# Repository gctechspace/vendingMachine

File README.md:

# vendingMachine

**************************Version 2******12/17***************
It's Been awhile ;-)
PCB needs a massive update!!! but will still work *enough*.
Moving to a Nextion 2.4" Touch Screen display and ditching the old Keypad.
Will probably move to an ESP32/8266 for Comms.
......More To Come

**************************Version 1******12/14***************
A Vending machine system using:
Atmega1284
Coin Selector <= Accepts 50c, $1 & $2
2.4" QVga tft <= Price & Info Display
SDCard	      <= Stock List & info
RFID Reader   <= For member discount & management functions
Breakouts for:
Bluetooth
NRF24L01 Radio's
ESP01 Wifi module
Intergrates with old keypad

Use's Shift registers to control despencing of Items.
Motors are multiplexed with Highside drivers and transistor arrays.
All Motor circuit have been changed to allow despence detection and allow
tray removal detection.

Project By...
SkipXtian
MickMorri
JamesSapsford
Spidie

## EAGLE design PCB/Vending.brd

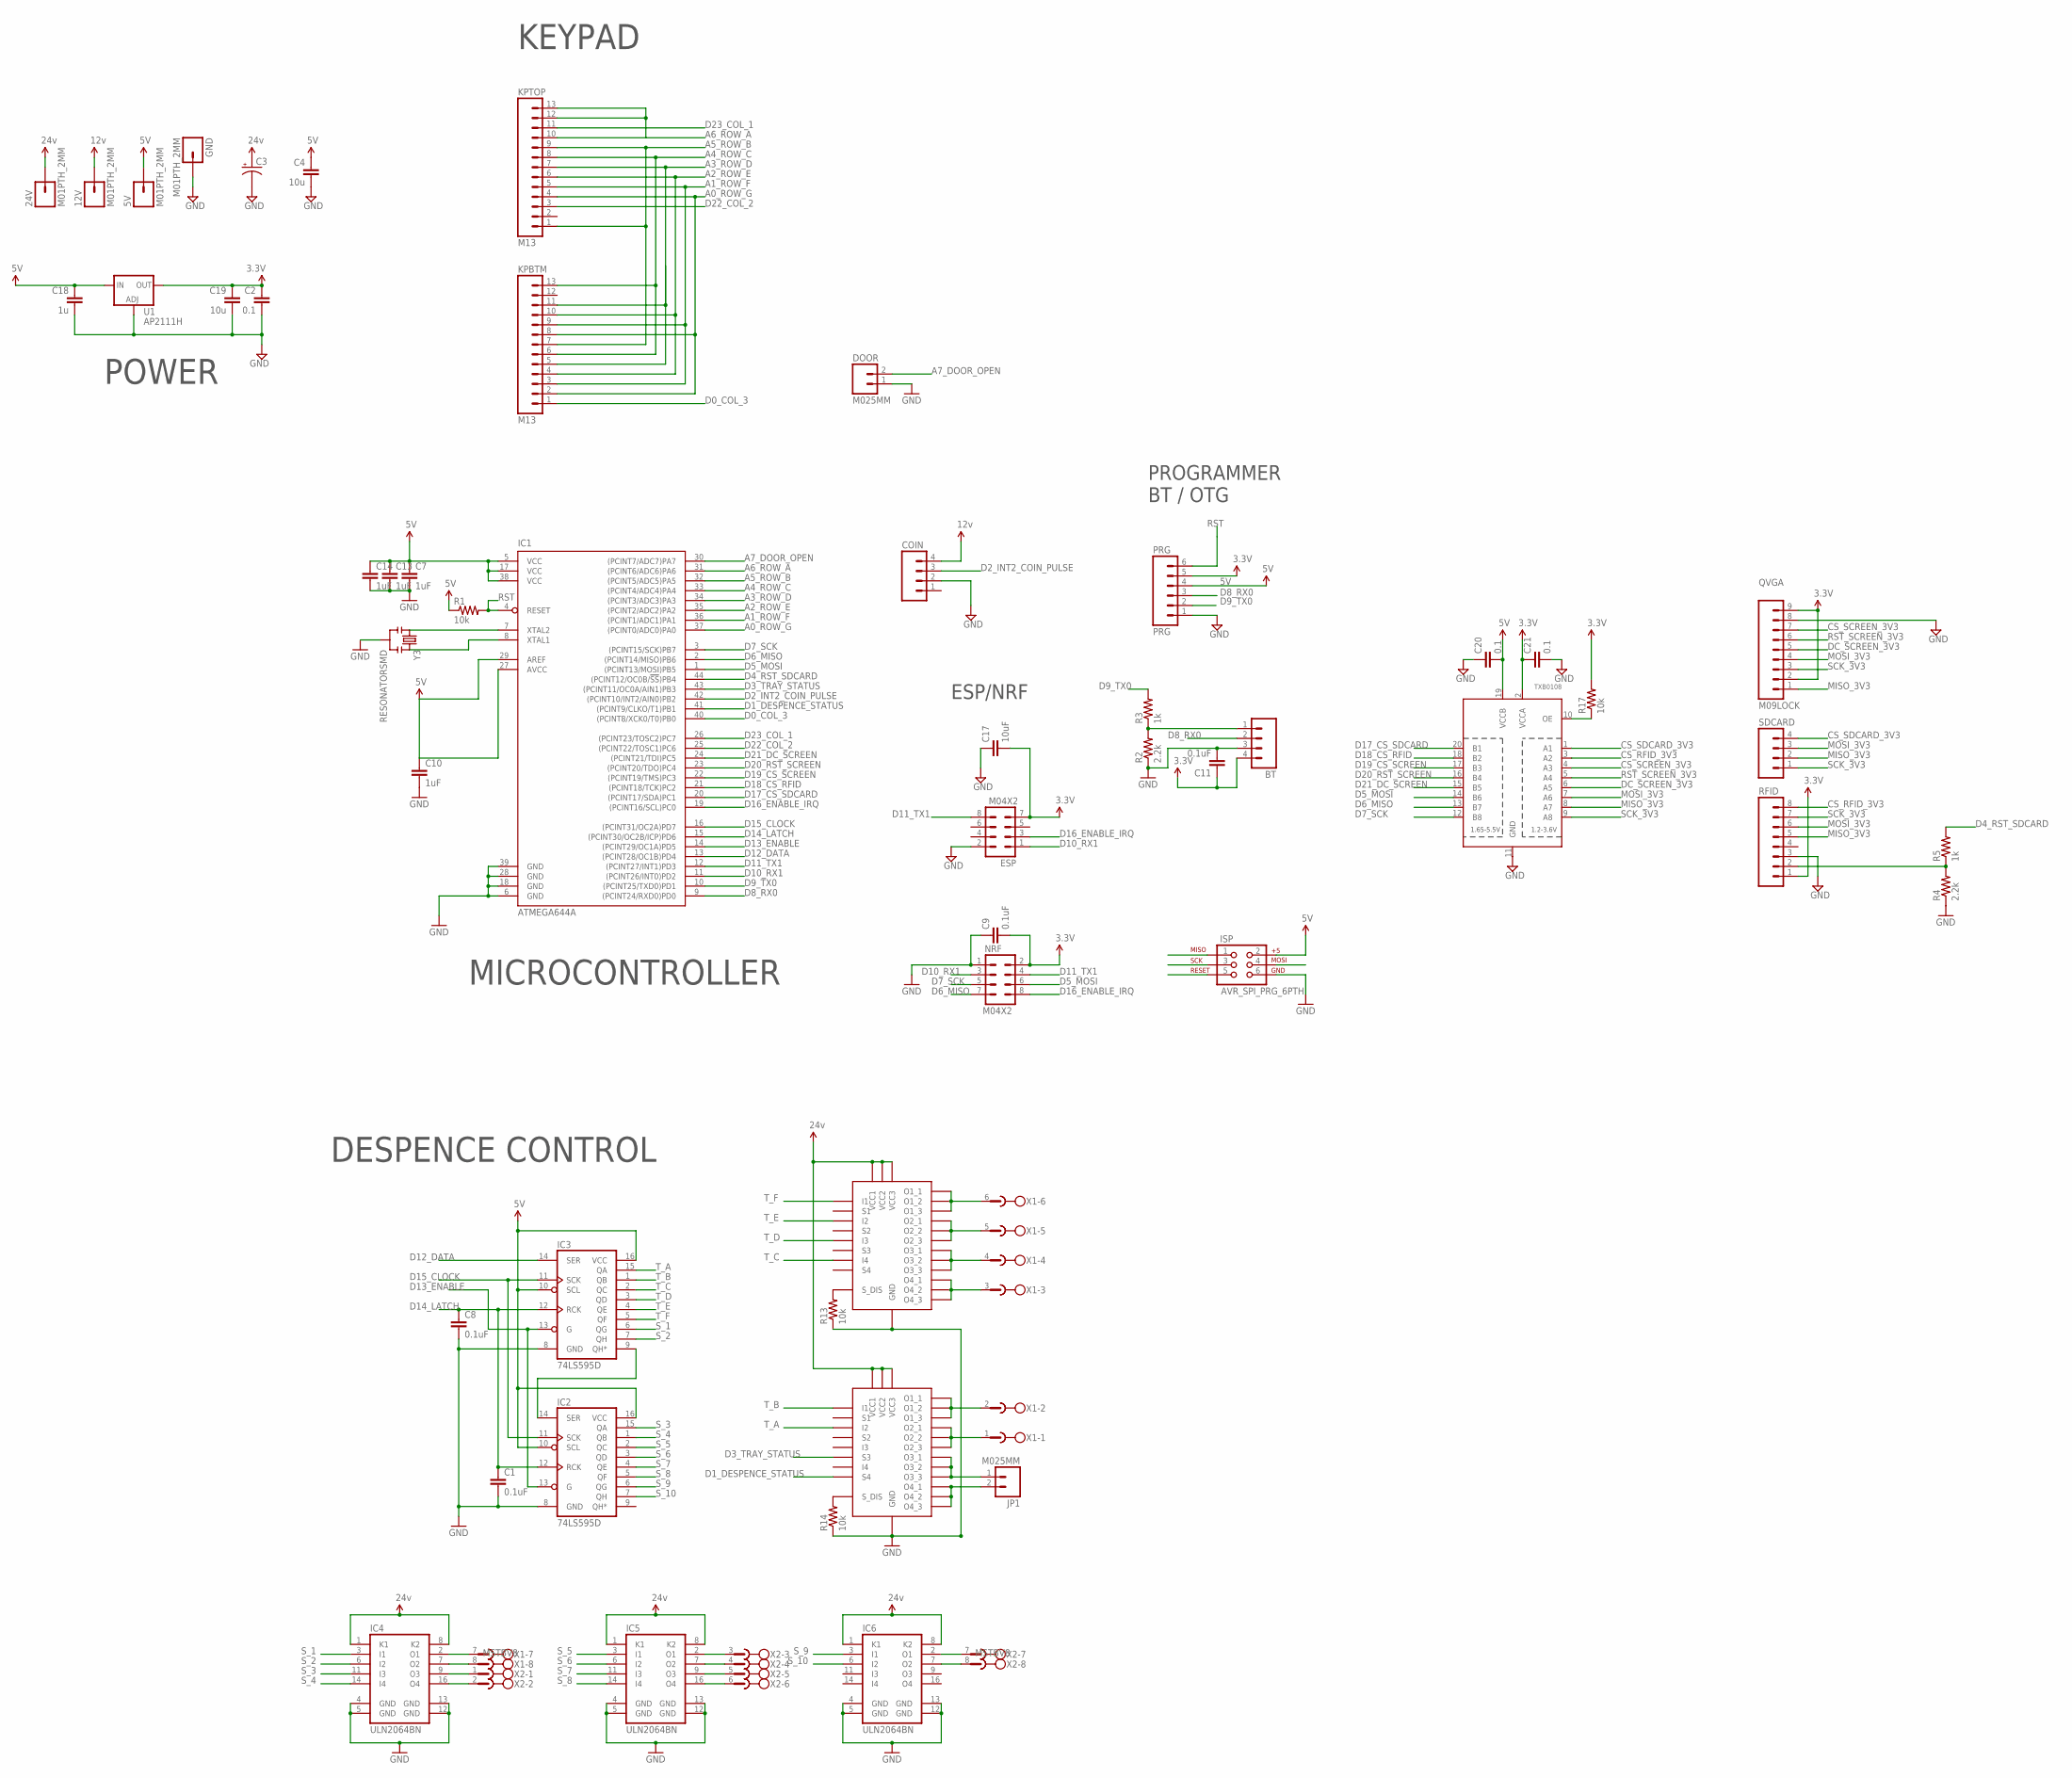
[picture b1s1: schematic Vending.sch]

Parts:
5V, 12V, 24V: M01PTH_2MM; 1X01_2MM
BT: M04PTH; 1X04
C1, C8, C9, C11: 0.1uF; 0805
C2, C20, C21: 0.1; 0805
C3: CAP_POLPTH4; CPOL-RADIAL-1000UF-25V
C4, C19: 10u; 0805-CAP
C7, C10, C13, C14: 1uF; 0805
C17: 10uF; 0805
C18: 1u; 0805
COIN: M04PTH; 1X04
DOOR: M025MM; SCREWTERMINAL-5MM-2
ESP: M04X2; 2X4
GND: M01PTH_2MM; 1X01_2MM
IC1: ATMEGA644A; TQFP44
IC2, IC3: 74LS595D; SO16
IC4, IC5, IC6: ULN2064BN; DIL16
ISP: AVR_SPI_PRG_6PTH; 2X3
JP1: M025MM; SCREWTERMINAL-5MM-2
KPBTM: M13; 1X13
KPTOP: M13; 1X13
NRF: M04X2; 2X4
PRG: PRG; 1X06
QVGA: M09LOCK; 1X09_LOCK
R1, R13, R14, R17: 10k; 0805
R2, R4: 2.2k; 0805
R3, R5: 1k; 0805
RFID: M08LOCK; 1X08_LOCK
SDCARD: M04LOCK; 1X04_LOCK
TXB0108: TXB0108PWR; TSSOP20
U1: AP2111H; SOT223
U$2, U$3: VNQ5E160K-E; POWERS0-24
X1: MSTBV8
X2: MSTBV8; MPN MSTBV 2,5/8-GF-5.08
Y3: RESONATORSMD; RESONATOR-SMD

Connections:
3.3V: BT.4, C2.1, C9.2, C11.1, C17.2, C19.1, C21.1, ESP.7, NRF.2, PRG.5, QVGA.2, QVGA.9, R17.2, RFID.1, TXB0108.2 (VCCA), U1.2 (OUT)
5V: 5V.1, C4.1, C7.1, C10.1, C13.1, C14.1, C18.1, C20.2, IC1.5 (VCC), IC1.17 (VCC), IC1.27 (AVCC), IC1.29 (AREF), IC1.38 (VCC), IC2.10 (SCL), IC2.16 (VCC), IC3.10 (SCL), IC3.16 (VCC), ISP.2, PRG.4, R1.1, TXB0108.19 (VCCB), U1.3 (IN)
12V: 12V.1, COIN.4
24V: 24V.1, C3.1 (+), IC4.1 (K1), IC4.8 (K2), IC5.1 (K1), IC5.8 (K2), IC6.1 (K1), IC6.8 (K2), U$2.1 (VCC1), U$2.12 (VCC2), U$2.VCC (VCC3), U$3.1 (VCC1), U$3.12 (VCC2), U$3.VCC (VCC3)
A0_ROW_G: IC1.37 ((PCINT0/ADC0)PA0), KPBTM.2, KPBTM.8, KPTOP.4
A1_ROW_F: IC1.36 ((PCINT1/ADC1)PA1), KPBTM.3, KPBTM.9, KPTOP.5
A2_ROW_E: IC1.35 ((PCINT2/ADC2)PA2), KPBTM.4, KPBTM.10, KPTOP.6
A3_ROW_D: IC1.34 ((PCINT3/ADC3)PA3), KPBTM.5, KPBTM.11, KPTOP.7
A4_ROW_C: IC1.33 ((PCINT4/ADC4)PA4), KPBTM.6, KPBTM.13, KPTOP.8
A5_ROW_B: IC1.32 ((PCINT5/ADC5)PA5), KPBTM.7, KPTOP.1, KPTOP.9
A6_ROW_A: IC1.31 ((PCINT6/ADC6)PA6), KPTOP.10, KPTOP.12, KPTOP.13
A7_DOOR_OPEN: DOOR.2, IC1.30 ((PCINT7/ADC7)PA7)
CS_RFID_3V3: RFID.8, TXB0108.3 (A2)
CS_SCREEN_3V3: QVGA.7, TXB0108.4 (A3)
CS_SDCARD_3V3: SDCARD.4, TXB0108.1 (A1)
D0_COL_3: IC1.40 ((PCINT8/XCK0/T0)PB0), KPBTM.1
D1_DESPENCE_STATUS: IC1.41 ((PCINT9/CLKO/T1)PB1), U$3.10 (S4)
D2_INT2_COIN_PULSE: COIN.3, IC1.42 ((PCINT10/INT2/AIN0)PB2)
D3_TRAY_STATUS: IC1.43 ((PCINT11/OC0A/AIN1)PB3), U$3.8 (S3)
D4_RST_SDCARD: IC1.44 ((PCINT12/OC0B/!SS!)PB4), R5.2
D5_MOSI: IC1.1 ((PCINT13/MOSI)PB5), ISP.4, NRF.6, TXB0108.14 (B6)
D6_MISO: IC1.2 ((PCINT14/MISO)PB6), ISP.1, NRF.7, TXB0108.13 (B7)
D7_SCK: IC1.3 ((PCINT15/SCK)PB7), ISP.3, NRF.5, TXB0108.12 (B8)
D8_RX0: BT.2, IC1.9 ((PCINT24/RXD0)PD0), PRG.3
D9_TX0: IC1.10 ((PCINT25/TXD0)PD1), PRG.2, R3.2
D10_RX1: ESP.1, IC1.11 ((PCINT26/INT0)PD2), NRF.3
D11_TX1: ESP.8, IC1.12 ((PCINT27/INT1)PD3), NRF.4
D12_DATA: IC1.13 ((PCINT28/OC1B)PD4), IC3.14 (SER)
D13_ENABLE: IC1.14 ((PCINT29/OC1A)PD5), IC2.13 (G), IC3.13 (G)
D14_LATCH: C1.1, C8.1, IC1.15 ((PCINT30/OC2B/ICP)PD6), IC2.12 (RCK), IC3.12 (RCK)
D15_CLOCK: IC1.16 ((PCINT31/OC2A)PD7), IC2.11 (SCK), IC3.11 (SCK)
D16_ENABLE_IRQ: ESP.3, IC1.19 ((PCINT16/SCL)PC0), NRF.8
D17_CS_SDCARD: IC1.20 ((PCINT17/SDA)PC1), TXB0108.20 (B1)
D18_CS_RFID: IC1.21 ((PCINT18/TCK)PC2), TXB0108.18 (B2)
D19_CS_SCREEN: IC1.22 ((PCINT19/TMS)PC3), TXB0108.17 (B3)
D20_RST_SCREEN: IC1.23 ((PCINT20/TDO)PC4), TXB0108.16 (B4)
D21_DC_SCREEN: IC1.24 ((PCINT21/TDI)PC5), TXB0108.15 (B5)
D22_COL_2: IC1.25 ((PCINT22/TOSC1)PC6), KPTOP.3
D23_COL_1: IC1.26 ((PCINT23/TOSC2)PC7), KPTOP.11
DC_SCREEN_3V3: QVGA.5, TXB0108.6 (A5)
GND: BT.3, C1.2, C2.2, C3.2 (-), C4.2, C7.2, C8.2, C9.1, C10.2, C11.2, C13.2, C14.2, C17.1, C18.2, C19.2, C20.1, C21.2, COIN.2, DOOR.1, ESP.2, GND.1, IC1.6 (GND), IC1.18 (GND), IC1.28 (GND), IC1.39 (GND), IC2.8 (GND), IC3.8 (GND), IC4.4 (GND), IC4.5 (GND), IC4.12 (GND), IC4.13 (GND), IC5.4 (GND), IC5.5 (GND), IC5.12 (GND), IC5.13 (GND), IC6.4 (GND), IC6.5 (GND), IC6.12 (GND), IC6.13 (GND), ISP.6, NRF.1, PRG.1, QVGA.8, R2.1, R4.1, R13.1, R14.1, RFID.3, TXB0108.11 (GND), U1.1 (ADJ), U$2.2 (GND), U$3.2 (GND), Y3.2
MISO_3V3: QVGA.1, RFID.5, SDCARD.2, TXB0108.8 (A7)
MOSI_3V3: QVGA.4, RFID.6, SDCARD.3, TXB0108.7 (A6)
unnamed: IC2.14 (SER), IC3.9 (QH*)
unnamed: IC1.7 (XTAL2), Y3.1
unnamed: IC1.8 (XTAL1), Y3.3
unnamed: IC4.9 (O3), X2.1
unnamed: IC4.2 (O1), X1.7
unnamed: BT.1, R2.2, R3.1
unnamed: IC4.7 (O2), X1.8
unnamed: IC4.16 (O4), X2.2
unnamed: IC5.2 (O1), X2.3
unnamed: IC5.7 (O2), X2.4
unnamed: IC6.2 (O1), X2.7
unnamed: IC6.7 (O2), X2.8
unnamed: R13.2, U$2.11 (S_DIS)
unnamed: R14.2, U$3.11 (S_DIS)
unnamed: R4.2, R5.1, RFID.2
unnamed: U$3.22 (O1_3), U$3.23 (O1_2), U$3.24 (O1_1), X1.2
unnamed: U$3.19 (O2_3), U$3.20 (O2_2), U$3.21 (O2_1), X1.1
unnamed: IC5.9 (O3), X2.5
unnamed: IC5.16 (O4), X2.6
unnamed: R17.1, TXB0108.10 (OE)
P1: U$2.22 (O1_3), U$2.23 (O1_2), U$2.24 (O1_1), X1.6
P2: U$2.19 (O2_3), U$2.20 (O2_2), U$2.21 (O2_1), X1.5
P3: U$2.16 (O3_3), U$2.17 (O3_2), U$2.18 (O3_1), X1.4
P4: U$2.13 (O4_3), U$2.14 (O4_2), U$2.15 (O4_1), X1.3
P7: JP1.1, U$3.16 (O3_3), U$3.17 (O3_2), U$3.18 (O3_1)
P8: JP1.2, U$3.13 (O4_3), U$3.14 (O4_2), U$3.15 (O4_1)
RST: IC1.4 (RESET), ISP.5, PRG.6, R1.2
RST_SCREEN_3V3: QVGA.6, TXB0108.5 (A4)
SCK_3V3: QVGA.3, RFID.7, SDCARD.1, TXB0108.9 (A8)
S_1: IC3.6 (QG), IC4.3 (I1)
S_2: IC3.7 (QH), IC4.6 (I2)
S_3: IC2.15 (QA), IC4.11 (I3)
S_4: IC2.1 (QB), IC4.14 (I4)
S_5: IC2.2 (QC), IC5.3 (I1)
S_6: IC2.3 (QD), IC5.6 (I2)
S_7: IC2.4 (QE), IC5.11 (I3)
S_8: IC2.5 (QF), IC5.14 (I4)
S_9: IC2.6 (QG), IC6.3 (I1)
S_10: IC2.7 (QH), IC6.6 (I2)
T_A: IC3.15 (QA), U$3.5 (I2)
T_B: IC3.1 (QB), U$3.3 (I1)
T_C: IC3.2 (QC), U$2.9 (I4)
T_D: IC3.3 (QD), U$2.7 (I3)
T_E: IC3.4 (QE), U$2.5 (I2)
T_F: IC3.5 (QF), U$2.3 (I1)

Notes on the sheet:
DESPENCE CONTROL
KEYPAD
MICROCONTROLLER
POWER
ESP/NRF
PROGRAMMER BT / OTG

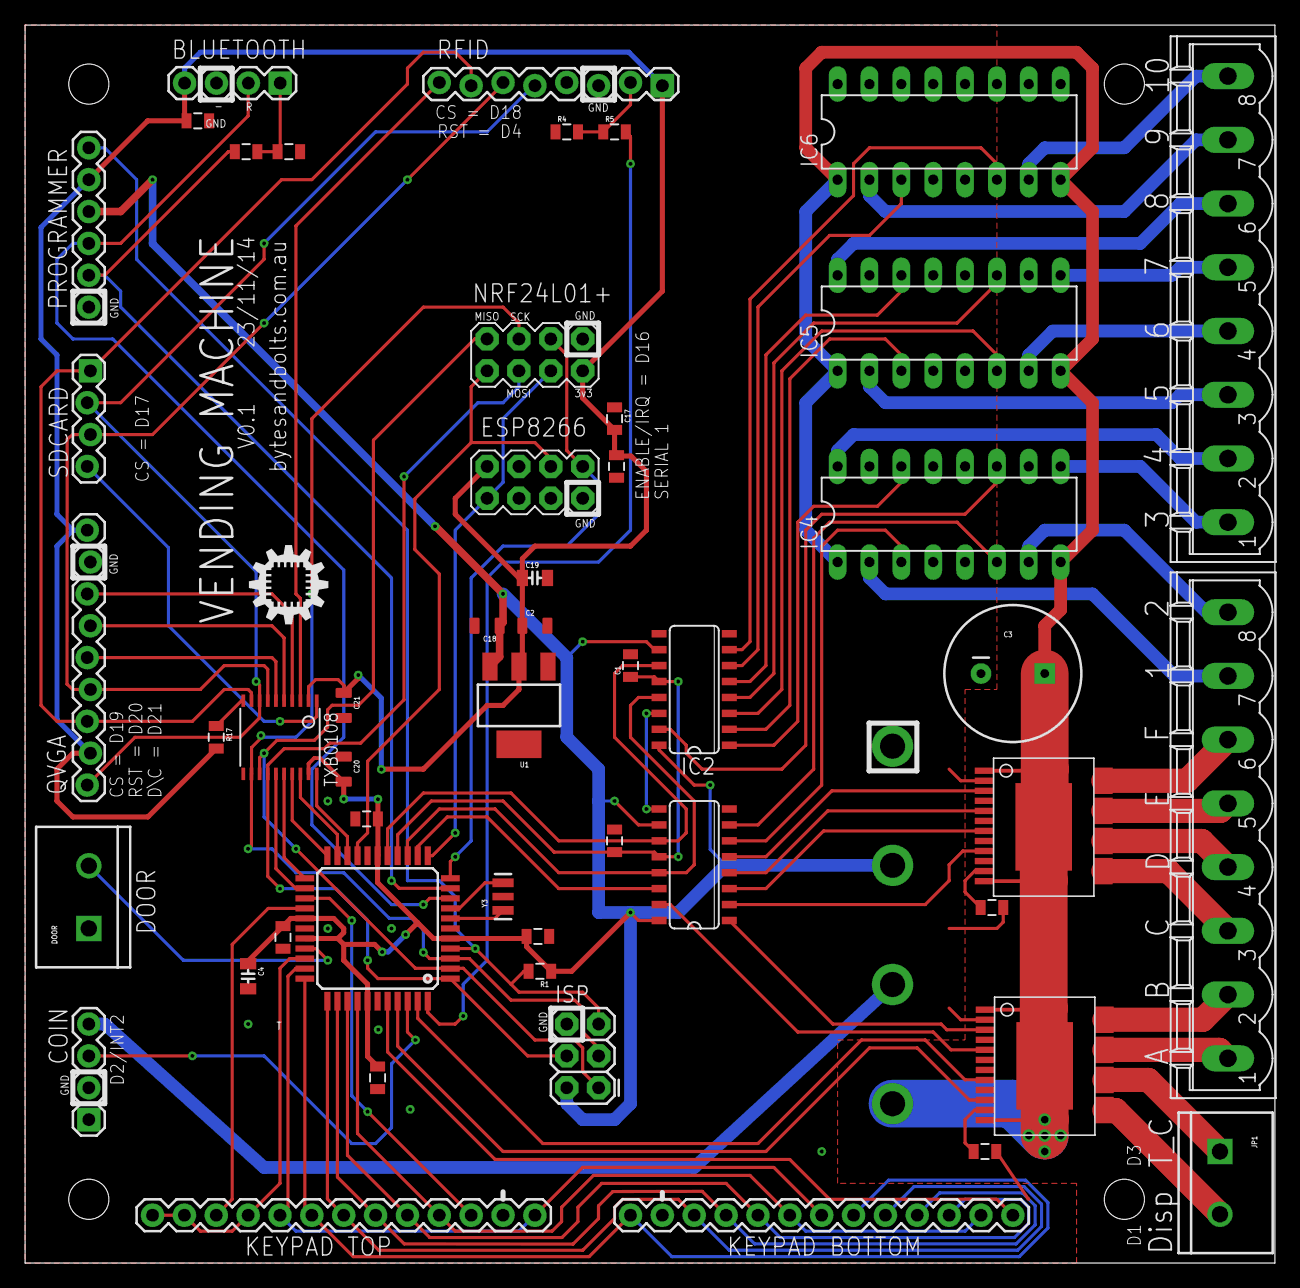
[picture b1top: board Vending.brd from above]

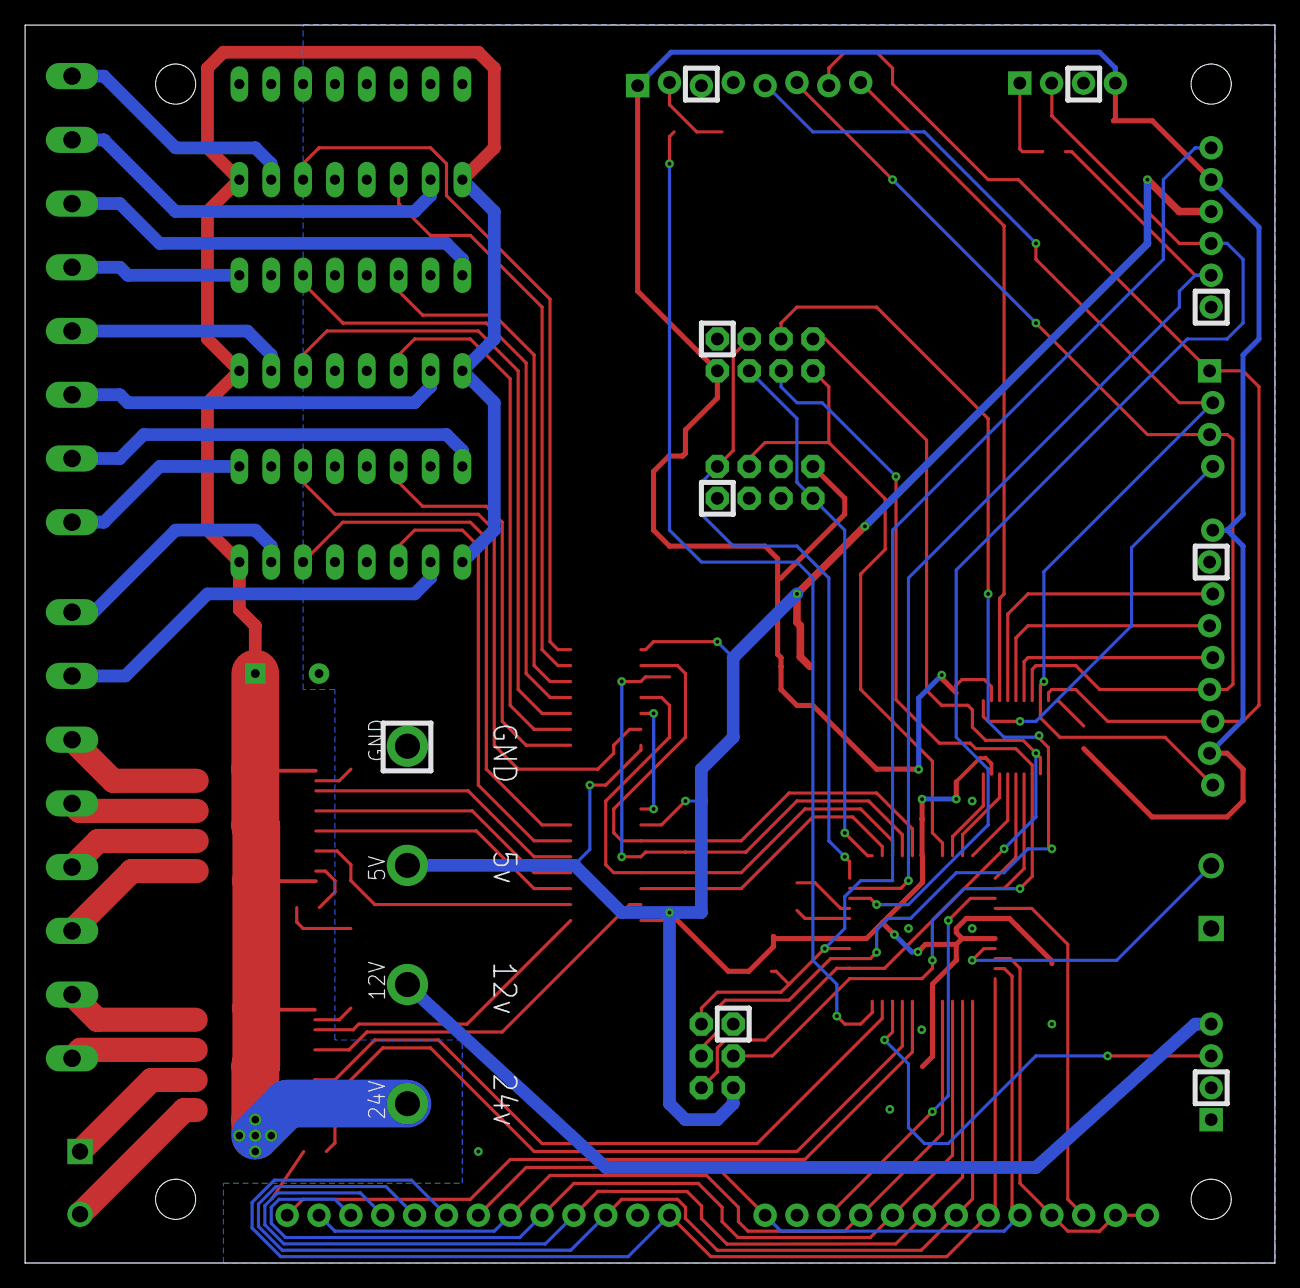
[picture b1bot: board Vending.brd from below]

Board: 2 copper layers, 99.6 x 98.7 mm, 55 parts (4 on the bottom side), 88 nets.

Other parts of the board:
U$1: ID_LOGO_X0.25

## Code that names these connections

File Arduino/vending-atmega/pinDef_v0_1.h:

//Pin defines for Board Version 0.1  -  23/11/14

//PB0-7
#define KP_Col3        0
#define despenceStatus 1 //24v so INVERTED
#define coinIn         2
#define trayStatus     3 //24v so INVERTED
#define RFID_RST       4 //MUST BE OUTPUT
#define HW_MOSI        5
#define HW_MISO        6
#define HW_SCK         7

//PD0-7
#define HW_Rx          8
#define HW_Tx          9
#define ESP_Rx         10
#define ESP_Tx         11
#define Shift_DATA     12
#define Shift_ENABLE   13
#define Shift_LATCH    14
#define Shift_CLOCK    15

//PC0-7
#define ESP_ENABLE     16
#define SDCard_CS      17
#define RFID_CS        18
#define QVGA_CS        19
#define QVGA_RST       20
#define QVGA_DC        21
#define KP_Col2        22
#define KP_Col1        23

//PA0-7
#define KP_RowG        24//A0
#define KP_RowF        25//A1
#define KP_RowE        26//A2
#define KP_RowD        27//A3
#define KP_RowC        28//A4
#define KP_RowB        29//A5
#define KP_RowA        30//A6
#define doorStatus     31//A7

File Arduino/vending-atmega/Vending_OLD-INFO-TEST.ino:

/* OLD CODE FOR TESTING MOTORS ETC - REFERENCE ONLY
const int enablePin = 13;
const int latchPin = 14;
const int clockPin = 15;
const int dataPin = 12;
const int IO1_Output = 11;
const int IO1_Status = 10;
const int IO2_Output = 26;
const int IO2_Status = 27;   //STATUS will go LOW when it has INPUT
const int IO3_Status = 1;
const int IO4_Status = 0;
const int IO5_Status = 23;
const int IO6_Status = 22;
const int IO7_Status = 21;
const int IO8_Status = 20;
const int IO9_Status = 19;
const int IO10_Status = 18;
const int watchDog = 16;

const int Selector = A0;  // Analog input pin that the voltage divider is attached to
const int selPwr = A1;    //Control of the NPN for the voltage dividers power

#define despenceTime 10000

void setup()
{
  //SETUP PORT INPUTS
  DDRC &= ~0xFC; //Set PC7-2 as OUTPUTS, FC=11111100  Doesn't affect the "0's"
  PORTC |= 0xFC; //Enable Pull Ups
  DDRB &= 0x03;  //set PB0-1 as OUTPUTS, 03=00000011
  PORTB |= 0x03;  //Enable Pull Ups
  DDRA &= 0xFC;
  //SETUP SHIFT REG
  //DDRD |= 0xF0;  //set PD4-7 as OUTPUTS, 0F=11110000
  //PORTD &= ~0x20; //set D13 (PD5) LOW
  pinMode(enablePin, OUTPUT);
  digitalWrite(enablePin, HIGH);  //Enabled Low = ON, HIGH = OFF
  pinMode(latchPin, OUTPUT);
  pinMode(dataPin, OUTPUT);
  pinMode(clockPin, OUTPUT);
  pinMode(IO1_Output, OUTPUT);  //D11
  pinMode(IO1_Status, INPUT);   //D10
  digitalWrite(IO1_Status, HIGH);     //Enable pull up
  pinMode(IO2_Output, OUTPUT);  //D26
  pinMode(IO2_Status, INPUT);   //D27
  digitalWrite(IO2_Status, HIGH);     //Enable pull up
  pinMode(watchDog, INPUT);  //SETUP PIN as watchDog


  Serial.begin(9600); //For Debugging & bluetooth
  Serial.println("Vending Test");



    pinMode(3, OUTPUT);

}

void loop()
{

  if(Serial.available() > 0) {
    byte traySelect = (1 << (Serial.read()-65)); //Converts the Row (A-F) into a binary (1-32)
    delay(100);
    byte slotSelect = processSlot(Serial.read());

    if(despence(traySelect, slotSelect)){
      Serial.println("Worked");
    } else {
      Serial.println("Error");
    }
  }
  //Serial.println(traySelect);
  //Serial.println(slotSelect);
}



byte processSlot(char inChar){
  if (inChar >= '1' && inChar <= '9'){
    return inChar-48;
  } else if (inChar == '0'){
    return 10;
  }
}

boolean despence(byte tray, byte slot){
  unsigned long despenceStart = 0;
  powerIO(tray);
  PORTA = (1 << (slot+1));  //the +1 is for testing as A2 is the first pin we are using on that port.
  despenceStart = millis();
  delay(100);
  //digitalWrite(A2, HIGH);
  while(digitalRead(IO10_Status)){
    if(millis() - despenceStart > despenceTime){
      powerIO(0);
      PORTA = 0x00; //All Off
      return false;
    }
  } //Get past the Low
  delay(200); //Debounce
  while(!digitalRead(IO10_Status)){
    if(millis() - despenceStart > despenceTime){
      powerIO(0);
      PORTA = 0x00; //All Off
      return false;
    }
  }  //Despence product
  delay(200); //Debounce
  powerIO(0);
  PORTA = 0x00; //All Off
  Serial.println(millis() - despenceStart);
  //digitalWrite(A2, LOW);
  return true;
}


//Turns Ports 3-10 ON/OFF
void powerIO(byte IOmap)  //pinout 3-10 int (1, 2, 4, 8, 16, 32, 64, 128)
{  //eg powerIO(16) turns IO7 ON, powerIO(34) turns 4 & 8 ON, powerIO(0) All OFF-ALWAYS DO THIS NOT JUST DISABLE
  digitalWrite(enablePin, LOW); //Turn Shift Reg ON
  digitalWrite(latchPin, LOW);
  shiftOut(dataPin, clockPin, LSBFIRST, IOmap);
  digitalWrite(latchPin, HIGH);
}
*/

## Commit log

2017-12-21 Using an Old PCB design to get the vending machine working
2017-12-21 Bit of a clean up
2018-04-25 Machine dispences, removed some unused code
2023-01-29 Add gcts-vending WordPress plugin
2023-01-29 Add vend WordPress theme
2023-01-29 Add README for WP stuff
2023-01-29 Uncommited changes
2023-01-29 Added the esp code
2023-02-01 Load stylesheet in theme
2023-02-01 Remove fields from checkout page
2023-02-01 Add vending checkout page + css + js
2023-02-01 Restrict dispense action to ordered quantity
2023-02-01 Update order status after dispense
2023-02-01 Copy template.php from plugin
2023-02-01 Tweak thank you page
2023-02-01 Make email button really big

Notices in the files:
parts and their libraries:
SparkFun-Resistors: Licensing: CC v3.0 Share-Alike You are welcome to use this library for commercial purposes.
